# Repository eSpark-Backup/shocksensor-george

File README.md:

# ShockSensor-George
 For Hardware and Software Development of ShockSensor-PCB for Spima Ltd.

## Project Documents
### New Design Proposal
https://docs.google.com/document/d/1cwAtrIecVFzTGOgoKfXupc5CIA_wZs_i1ySnAws0fEk/edit?usp=sharing

### Current Design Rework
https://docs.google.com/document/d/1-ERZRN2x7w0QCunjctplsGUNkxZJDdCkyaSeu2aAGT0/edit#heading=h.7z0ya98mlv53

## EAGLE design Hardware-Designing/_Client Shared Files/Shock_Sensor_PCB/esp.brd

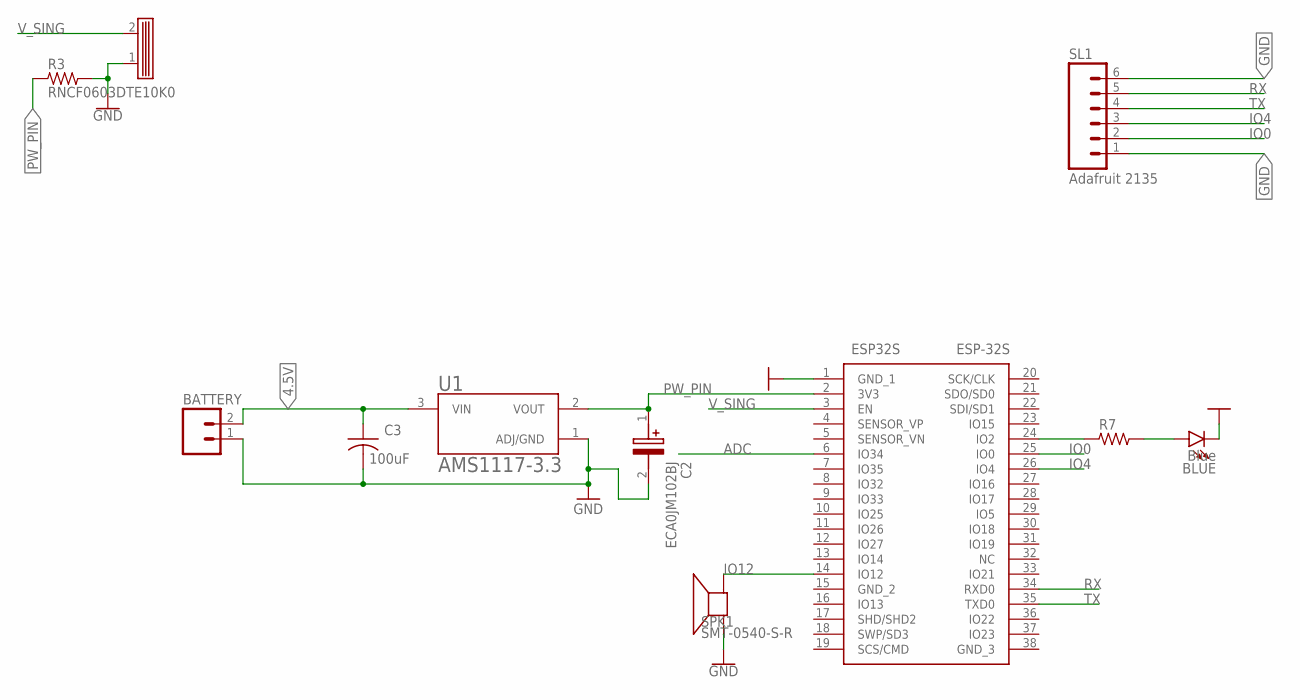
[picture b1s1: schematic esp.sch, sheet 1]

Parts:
BATTERY: MP-4-3 TAKACHI ELECTRONICS ENCLOSURE TAKACHI ELEC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; 02P
BLUE: Blue; LED3MM
C2: ECA0JM102BJ; CAPPRD350W65D825H1250
C3: 100uF; C0805K
ESP32S: ESP-32S
R3: RNCF0603DTE10K0; R0603
R7: ERJ-UP3J221V; R0201
SL1: Adafruit 2135; 06P
SPK1: SMT-0540-S-R
U1: AMS1117-3.3; SOT229P700X180-4N
U$1: SW-18015P

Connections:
4.5V: BATTERY.2, C3.1, U1.3 (VIN); also elsewhere on the board
4.5V1: ESP32S.24 (IO2), R7.1
ADC: ESP32S.6 (IO34); also elsewhere on the board
GND: BATTERY.1, BLUE.K (C), C2.2 (-), C3.2, ESP32S.1 (GND_1), R3.2, SL1.1, SL1.6, SPK1.- (+), U1.1 (ADJ/GND), U$1.1 (+VE); also elsewhere on the board
IO0: ESP32S.25 (IO0), SL1.2
IO4: ESP32S.26 (IO4), SL1.3
IO12: ESP32S.14 (IO12), SPK1.+ (-)
unnamed: BLUE.A, R7.2
PW_PIN: C2.1 (+), ESP32S.2 (3V3), R3.1, U1.2 (VOUT)
RX: ESP32S.34 (RXD0), SL1.5
TX: ESP32S.35 (TXD0), SL1.4
V_SING: ESP32S.3 (EN), U$1.2 (-VE)

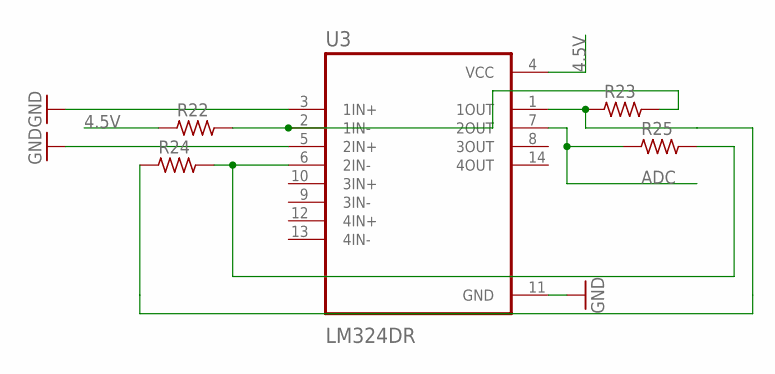
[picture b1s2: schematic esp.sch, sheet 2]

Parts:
R22: RMCF0201JT6K20; R0201
R23, R24, R25: RC0201JR-0710KL; R0201
U3: LM324DR; SOIC127P600X175-14N

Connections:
4.5V: R22.1, U3.4 (VCC); also elsewhere on the board
ADC: R25.1, U3.7 (2OUT); also elsewhere on the board
GND: U3.3 (1IN+), U3.5 (2IN+), U3.11 (GND); also elsewhere on the board
unnamed: R22.2, R23.2, U3.2 (1IN-)
unnamed: R24.2, R25.2, U3.6 (2IN-)
unnamed: R23.1, R24.1, U3.1 (1OUT)

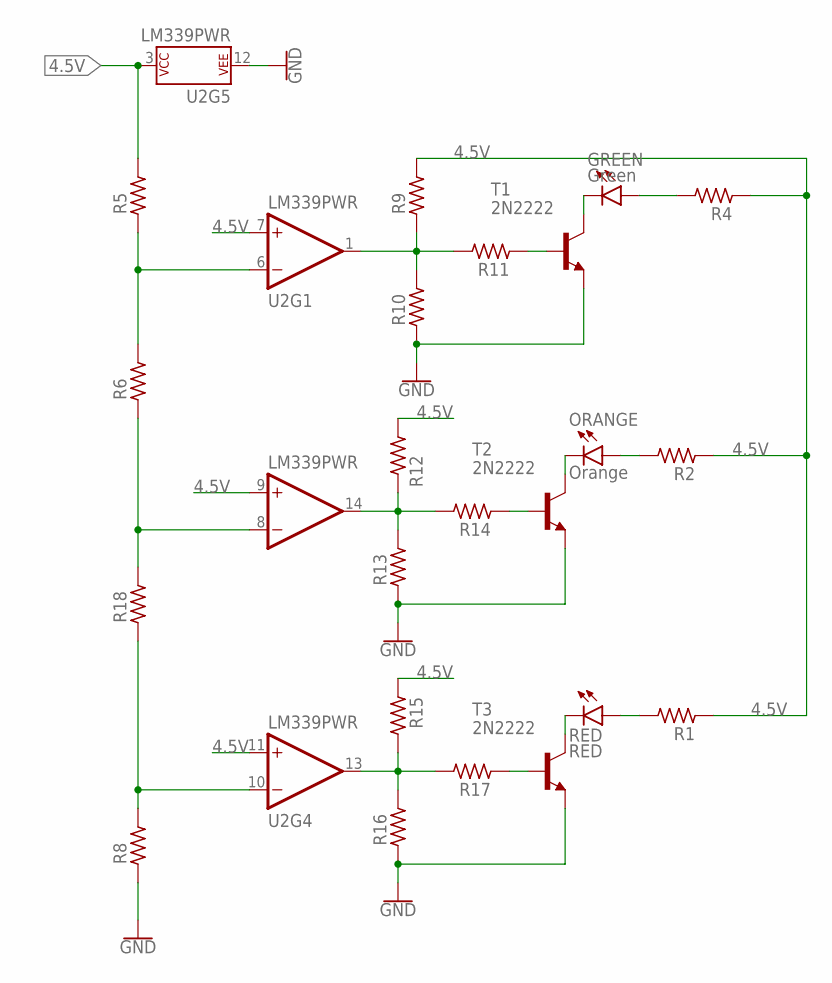
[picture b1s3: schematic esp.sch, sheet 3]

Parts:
GREEN: Green; LED3MM
ORANGE: Orange; LED3MM
R1, R2, R4: ERJ-UP3J221V; R0201
R5, R8, R9, R10, R11, R12, R13, R14, R15, R16, R17: RMCF0201JT10K0; R0201
R6: RMCF0201JT20K0; R0201
R18: PNM0805E5002BST5; C0805
RED: RED; LED3MM
T1, T2, T3: 2N2222; TO92-EBC-OVAL
U2: LM339PWR; TSSOP-14

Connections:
4.5V: R1.1, R2.1, R4.1, R5.2, R9.2, R12.1, R15.1, U2.3 (P$V+), U2.7 (+IN), U2.9 (+IN), U2.11 (+IN); also elsewhere on the board
GND: R8.1, R10.1, R13.1, R16.1, T1.E, T2.E, T3.E, U2.12 (P$V-); also elsewhere on the board
unnamed: GREEN.A, R4.2
unnamed: ORANGE.A, R2.2
unnamed: R1.2, RED.A
unnamed: R8.2, R18.1, U2.10 (-IN)
unnamed: R6.1, R18.2, U2.8 (-IN)
unnamed: R5.1, R6.2, U2.6 (-IN)
unnamed: R9.1, R10.2, R11.2, U2.1 (OUT)
unnamed: R12.2, R13.2, R14.2, U2.14 (OUT)
unnamed: R15.2, R16.2, R17.2, U2.13 (OUT)
unnamed: R11.1, T1.B
unnamed: R14.1, T2.B
unnamed: R17.1, T3.B
unnamed: GREEN.K (C), T1.C
unnamed: ORANGE.K (C), T2.C
unnamed: RED.K (C), T3.C

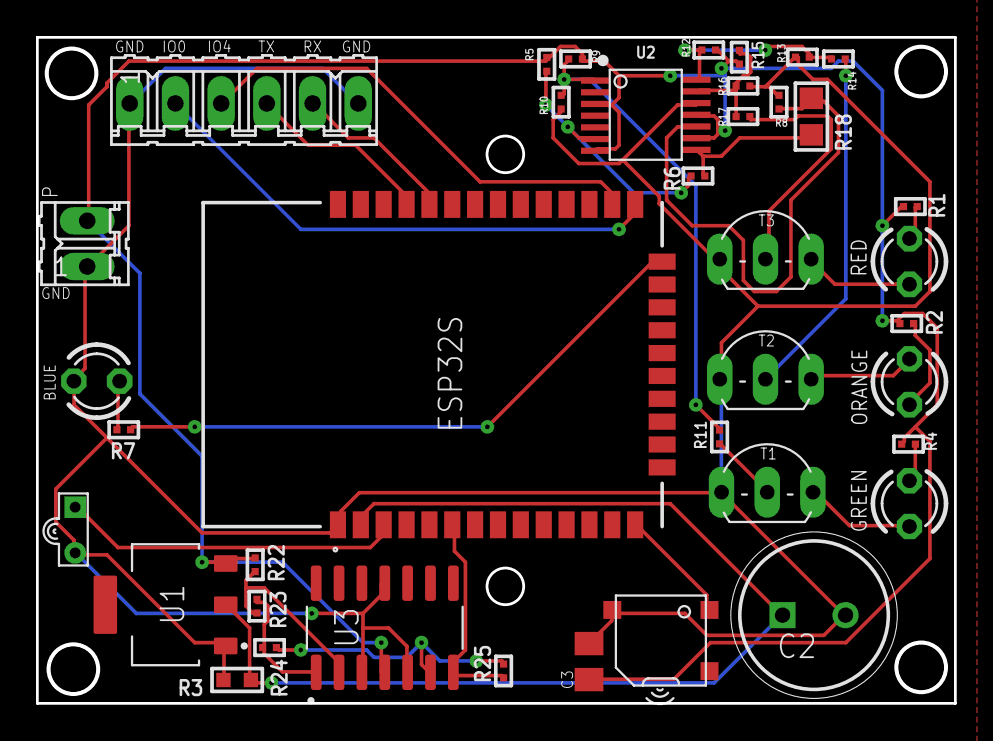
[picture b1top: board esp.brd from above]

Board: 2 copper layers, 50.9 x 36.9 mm, 39 parts (0 on the bottom side), 30 nets.

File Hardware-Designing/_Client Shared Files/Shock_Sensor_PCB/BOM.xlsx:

Part | Value | Device | Package | Description
BATTERY | MP-4-3 TAKACHI ELECTRONICS ENCLOSURE TAKACHI ELECTRONICS ENCLOSURE | M02 | 02P | AMP QUICK CONNECTOR
BLUE | Blue | LED3MM | LED3MM | LED
C2 | ECA0JM102BJ | ECA0JM102BJ | CAPPRD350W65D825H1250 | Cap Aluminum Lytic 1000uF 6.3V 20% (8 X 11.5mm) Radial 580mA 2000h 85C
C3 | 100uF | C-USC0805K | C0805K | CAPACITOR, American symbol
ESP32S | ESP-32S | ESP-32S | ESP-32S | WiFi-BT-BLE MCU module
GREEN | Green | LED3MM | LED3MM | LED
ORANGE | Orange | LED3MM | LED3MM | LED
R1 | ERJ-UP3J221V | R_0201 | R0201 | RESISTOR
R2 | ERJ-UP3J221V | R_0201 | R0201 | RESISTOR
R3 | RNCF0603DTE10K0 | R_0603 | R0603 | RESISTOR
R4 | ERJ-UP3J221V | R_0201 | R0201 | RESISTOR
R5 | RMCF0201JT10K0 | R_0201 | R0201 | RESISTOR
R6 | RMCF0201JT20K0 | R_0201 | R0201 | RESISTOR
R7 | ERJ-UP3J221V | R_0201 | R0201 | RESISTOR
R8 | RMCF0201JT10K0 | R_0201 | R0201 | RESISTOR
R9 | RMCF0201JT10K0 | R_0201 | R0201 | RESISTOR
R10 | RMCF0201JT10K0 | R_0201 | R0201 | RESISTOR
R11 | RMCF0201JT10K0 | R_0201 | R0201 | RESISTOR
R12 | RMCF0201JT10K0 | R_0201 | R0201 | RESISTOR
R13 | RMCF0201JT10K0 | R_0201 | R0201 | RESISTOR
R14 | RMCF0201JT10K0 | R_0201 | R0201 | RESISTOR
R15 | RMCF0201JT10K0 | R_0201 | R0201 | RESISTOR
R16 | RMCF0201JT10K0 | R_0201 | R0201 | RESISTOR
R17 | RMCF0201JT10K0 | R_0201 | R0201 | RESISTOR
R18 | PNM0805E5002BST5 | R_0805 | C0805 | RESISTOR
R22 | RMCF0201JT6K20 | R_0201 | R0201 | RESISTOR
R23 | RC0201JR-0710KL | R_0201 | R0201 | RESISTOR
R24 | RC0201JR-0710KL | R_0201 | R0201 | RESISTOR
R25 | RC0201JR-0710KL | R_0201 | R0201 | RESISTOR
RED | RED | LED3MM | LED3MM | LED
SL1 | Adafruit 2135 | M06 | 06P | AMP QUICK CONNECTOR
SPK1 | SMT-0540-S-R | SMT-0540-S-R | SMT-0540-S-R | SMT-0549-S-R
T1 | 2N2222 | 2N2222 | TO92-EBC-OVAL | NPN TRANSISTOR
T2 | 2N2222 | 2N2222 | TO92-EBC-OVAL | NPN TRANSISTOR
T3 | 2N2222 | 2N2222 | TO92-EBC-OVAL | NPN TRANSISTOR
U$1 | SW-18015P | SW-18015P | SW-18015P
U1 | AMS1117-3.3 | AMS1117-3.3 | SOT229P700X180-4N | Sot223/Pkg 1-Amp 3.3-Volt Low Drop Out Voltage Regulatator
U2 | LM339PWR | LM339 | TSSOP-14 | Quad Comparator - LM339PWR
U3 | LM324DR | LM324DR | SOIC127P600X175-14N | Check prices

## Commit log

2021-03-16 Added all the Project Files and Folders.
2021-05-05 Requirements Document
2021-07-14 Latest Files and Folders
2021-07-24 Issues Document
2021-08-21 Firmware Uploaded (From Abbas)
2021-08-21 URL changed in Firmware; Tested
2021-08-27 George code
    battery Status + LED + Buzzer + functions to push data to cloud.
2021-08-30 George code
    code is correctly adding data into incident table at data base.
2021-08-30 George code
    All functions are working
2021-08-31 Changed Folder Locations
2021-08-31 George code
    Battery Status Test Code + Battery status code added to final code.
2021-09-02 Proposal link added to Readme
2021-09-03 Battery status added to cloud
    //
2021-09-06 Library_creation
2021-09-07 Schematic Design and some parts addition in Library
2021-09-08 Schematic design and Parts addition
2021-09-08 Deep-Sleep-LED-Test
    //
2021-09-08 Design Reviewed; Readme and .gitignore modified
2021-09-09 Changes in Schematic
2021-09-09 latest Changes in Schematic
2021-09-09 Latest Changes in Schematic design
2021-09-09 Changes in signals at sensor pins
2021-09-10 PCB Parts Placement and Routing
2021-09-10 Updated BOM (Digikey BOM) Completed ,(LCSC BOM) Remaining.
2021-09-13 PCB ROUTING
2021-09-14 Updated Library
2021-09-16 Changes in Schematic and PCB Routing
2021-09-18 Dimension of PCB
2021-09-20 updating LCSC BOM(Still remaing)
2021-09-21 Updated BOM LCSC Or Digikey
2021-09-25 PCB and Schematic updated Acc to library changes
2021-10-01 latest library
2021-10-02 led and battery points placement
2021-10-04 Updated library and Schematic all TH LED are corrected and replays in Schematic.
2021-10-04 PCB updated according toLibrary changes
2021-10-05 esp32-s-ai datasheet added to client files.
2021-10-08 LEDs Updated in Library schematic and PCB
2021-10-09 PCB updated acc to review
2021-10-11 Latest file
2021-10-11 ESP32 and USB updated in PCB
2021-10-11 Production_File
2021-10-11 Latest BOM
2021-10-13 LCSC and DigiKey BOMs reviewed and updated.
2021-10-14 Generated Design PDF
2021-10-23 Latest Files Esp32 Change Library and Schematic
2021-10-23 Latest Files 3d Body change ESP32
2021-10-23 PCB updated according to changes
2021-10-28 3D body of sensor(SW-420) updated in PCB
2021-10-29 PCB Updated and Deliverables
2021-11-02 Latest PDF Created
2021-11-02 Updated PDF PCB Section remove
2021-11-03 Step files created. New Gerber and NC Drill Files created.
2021-11-10 Digikey BOM update kr dia ha LCSC BOM remaining ha
2021-11-11 #10 LCSC BOM Update kr dia ha jo parts LCSC per Non stock han wo Quotation k lye issue per mention kr diye han
2021-11-25 Fresh Deliverables Generated
2022-02-07 tested detect shocks
2022-02-08 #17 Resolved, netlabels corrected
2022-02-08 Netlabel names also changed in PCB; no deliverables creating needed
2022-02-08 added code for LED test, Sleep test and shock detection
2022-02-14 added battery monitoring code in Final code - remaining testing
2022-02-14 Tested successfully integration of battery monitoring to existing code
2022-02-15 improvised code -reduced current consumption and wakeup time
2022-02-15 added library function prototypes
2022-02-15 completed and tested ShockSensor Library
2022-02-17 latest George code, battery optimized and avoids resetting
2022-02-19 update library to use ArduinoJson6
2022-02-23 #20 Completed
2022-02-23 corrections in issue #20
2022-02-25 Parts Placement and routing acc #22
2022-02-26 Minor Changes in PCB after review. Refer to PCB Designing-Review of PCB #24
2022-02-26 minor changes done in PCBacc #24
2022-02-28 Schematic Restructured. #21
2022-02-28 #23 Completed.
2022-03-02 Changes done acc: #25
2022-03-07 Deliverables generated(Pick and Place file is remaining)
2022-03-08 Pick and Place Files generated #26
2022-03-08 #27 Completed

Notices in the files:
parts and their libraries:
rc-master-smd: Copyright (C) 2007, Bob Starr
SparkFun-IC-Amplifiers: Licensing: Creative Commons ShareAlike 4.0 International - https://creativecommons.org/licenses/by-sa/4.0
